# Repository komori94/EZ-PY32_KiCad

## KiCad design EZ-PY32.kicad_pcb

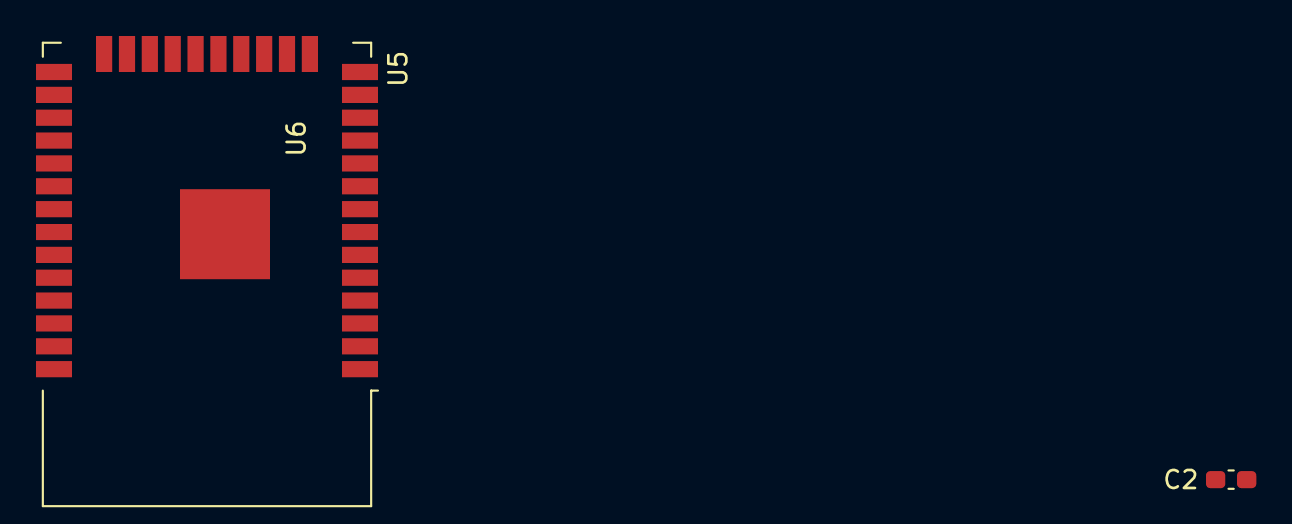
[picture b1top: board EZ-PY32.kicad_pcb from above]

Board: 2 copper layers, 4 parts (1 on the bottom side), 8 nets, no tracks yet.

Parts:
C2: 10nF; C_0603_1608Metric_Pad1.08x0.95mm_HandSolder
J3: Conn_02x08_Odd_Even; HTSS-108-01-YY-DV
U5: ESP32-WROOM-32
U6: 3.5; kuman_display_3.5zoll

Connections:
+3V3: J3.10, U5.2
/Anschlüssse/SCL: J3.4, U5.30
/Anschlüssse/SDA: J3.2, U5.29
/Drehencoder/Potti_B: C2.2, U5.6
GND: C2.1, J3.6, U5.1, U5.15, U5.38, U5.39
SENSOR_VN: J3.11, U5.5
SENSOR_VP: J3.13, U5.4
Tx: J3.14, U5.35

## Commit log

2020-11-08 Start
2020-11-27 Datenblätter hinzufügen und anschlüsse beschriften
2020-12-23 i did everithing
2020-12-23 logo einfügen
2020-12-28 relocating display
2021-01-06 smal fixes
2021-01-06 renamed logo data name
2021-01-28 Add CAD
